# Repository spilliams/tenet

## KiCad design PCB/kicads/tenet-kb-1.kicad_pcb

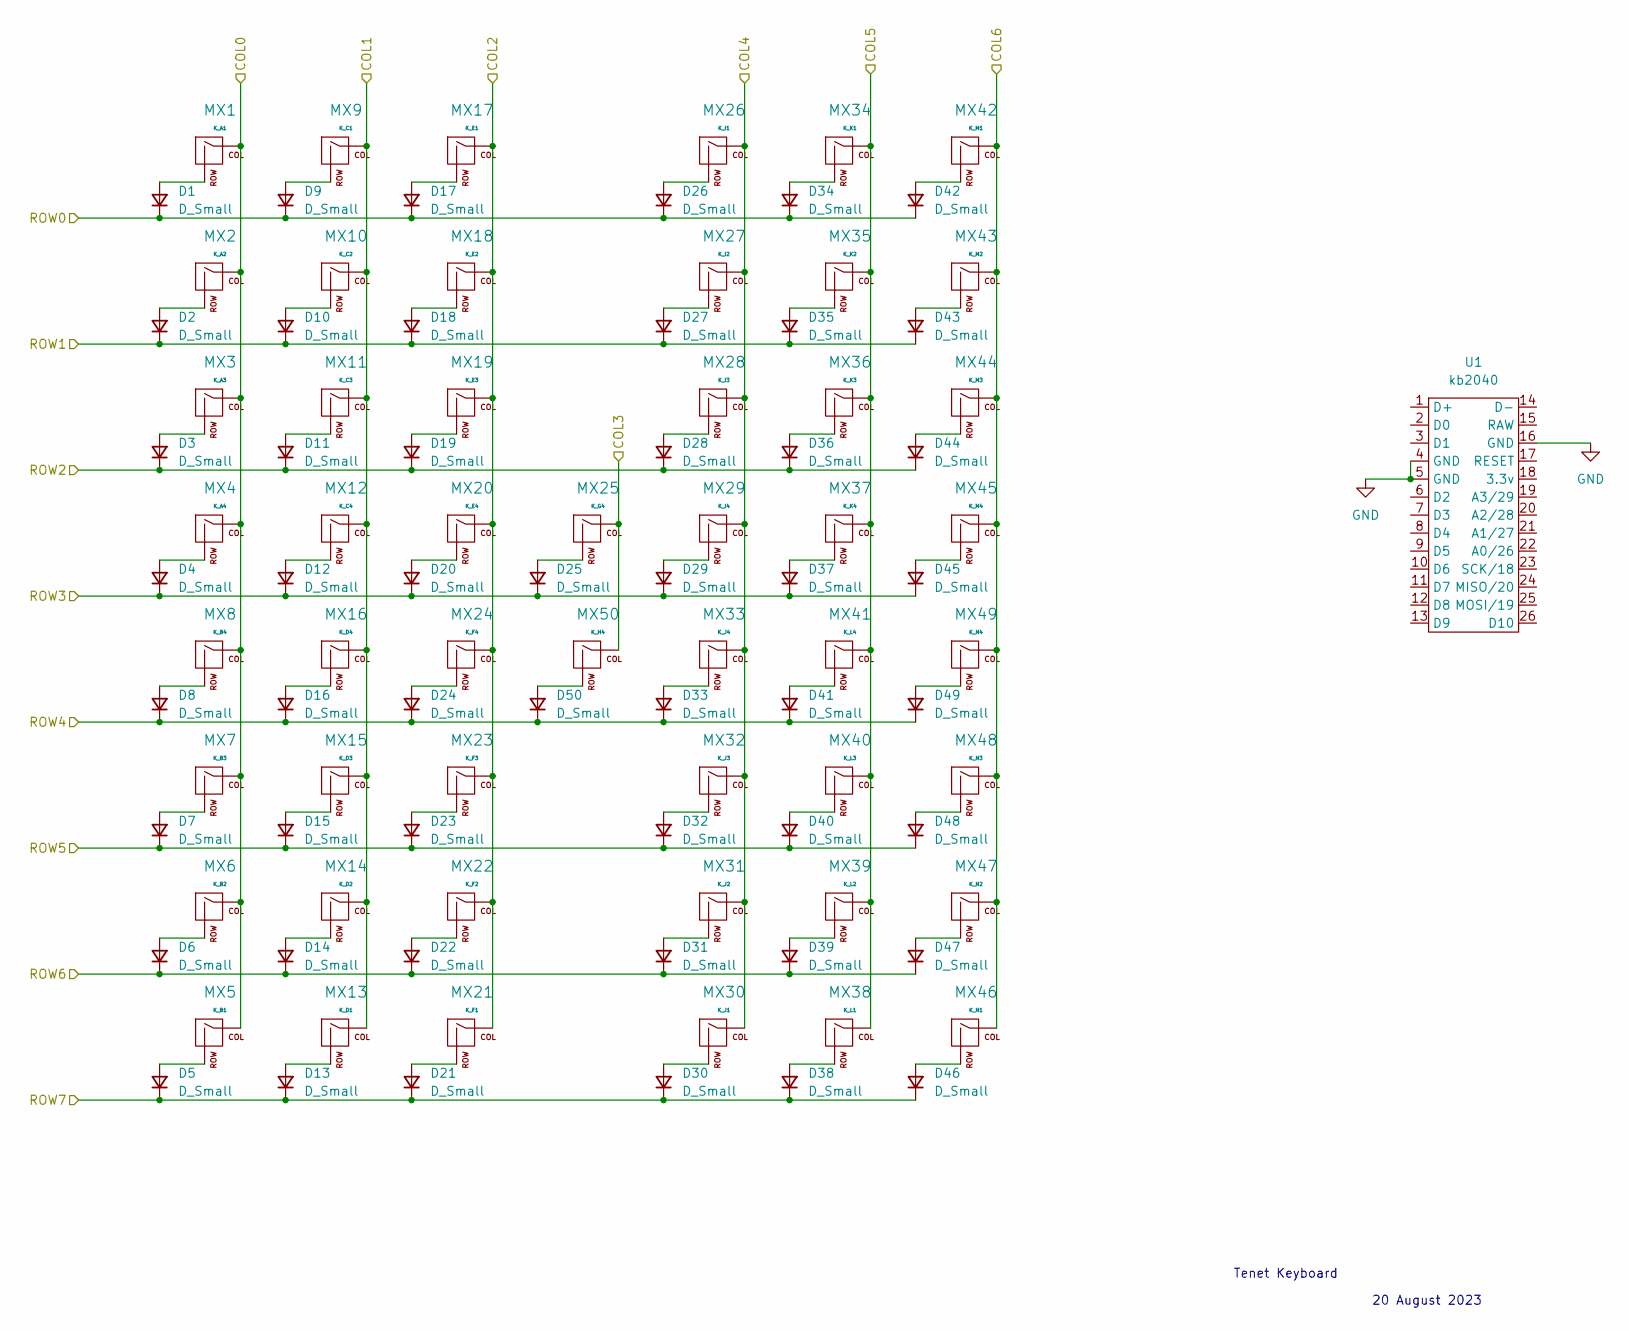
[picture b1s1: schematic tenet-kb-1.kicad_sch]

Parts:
D1, D2, D3, D4, D5, D6, D7, D8, D9, D10, D11, D12, D13, D14, D15, D16, D17, D18, D19, D20, D21, D22, D23, D24, D25, D26, D27, D28, D29, D30, D31, D32, D33, D34, D35, D36, D37, D38, D39, D40, D41, D42, D43, D44, D45, D46, D47, D48, D49, D50: D_Small; D_SOD-123
MX1: K_A1; Kailh_socket_PG1350
MX2: K_A2; Kailh_socket_PG1350
MX3: K_A3; Kailh_socket_PG1350
MX4: K_A4; Kailh_socket_PG1350
MX5: K_B1; Kailh_socket_PG1350
MX6: K_B2; Kailh_socket_PG1350
MX7: K_B3; Kailh_socket_PG1350
MX8: K_B4; Kailh_socket_PG1350
MX9: K_C1; Kailh_socket_PG1350
MX10: K_C2; Kailh_socket_PG1350
MX11: K_C3; Kailh_socket_PG1350
MX12: K_C4; Kailh_socket_PG1350
MX13: K_D1; Kailh_socket_PG1350
MX14: K_D2; Kailh_socket_PG1350
MX15: K_D3; Kailh_socket_PG1350
MX16: K_D4; Kailh_socket_PG1350
MX17: K_E1; Kailh_socket_PG1350
MX18: K_E2; Kailh_socket_PG1350
MX19: K_E3; Kailh_socket_PG1350
MX20: K_E4; Kailh_socket_PG1350
MX21: K_F1; Kailh_socket_PG1350
MX22: K_F2; Kailh_socket_PG1350
MX23: K_F3; Kailh_socket_PG1350
MX24: K_F4; Kailh_socket_PG1350
MX25: K_G4; Kailh_socket_PG1350
MX26: K_I1; Kailh_socket_PG1350
MX27: K_I2; Kailh_socket_PG1350
MX28: K_I3; Kailh_socket_PG1350
MX29: K_I4; Kailh_socket_PG1350
MX30: K_J1; Kailh_socket_PG1350
MX31: K_J2; Kailh_socket_PG1350
MX32: K_J3; Kailh_socket_PG1350
MX33: K_J4; Kailh_socket_PG1350
MX34: K_K1; Kailh_socket_PG1350
MX35: K_K2; Kailh_socket_PG1350
MX36: K_K3; Kailh_socket_PG1350
MX37: K_K4; Kailh_socket_PG1350
MX38: K_L1; Kailh_socket_PG1350
MX39: K_L2; Kailh_socket_PG1350
MX40: K_L3; Kailh_socket_PG1350
MX41: K_L4; Kailh_socket_PG1350
MX42: K_M1; Kailh_socket_PG1350
MX43: K_M2; Kailh_socket_PG1350
MX44: K_M3; Kailh_socket_PG1350
MX45: K_M4; Kailh_socket_PG1350
MX46: K_N1; Kailh_socket_PG1350
MX47: K_N2; Kailh_socket_PG1350
MX48: K_N3; Kailh_socket_PG1350
MX49: K_N4; Kailh_socket_PG1350
MX50: K_H4; Kailh_socket_PG1350
U1: kb2040

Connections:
3.3V: U1.17 (RESET)
/COL0: MX1.1 (COL), MX2.1 (COL), MX3.1 (COL), MX4.1 (COL), MX5.1 (COL), MX6.1 (COL), MX7.1 (COL), MX8.1 (COL), U1.18 (3.3v)
/COL1: MX9.1 (COL), MX10.1 (COL), MX11.1 (COL), MX12.1 (COL), MX13.1 (COL), MX14.1 (COL), MX15.1 (COL), MX16.1 (COL), U1.20 (A2/28)
/COL2: MX17.1 (COL), MX18.1 (COL), MX19.1 (COL), MX20.1 (COL), MX21.1 (COL), MX22.1 (COL), MX23.1 (COL), MX24.1 (COL), U1.11 (D7)
/COL3: MX25.1 (COL), MX50.1 (COL), U1.13 (D9)
/COL4: MX26.1 (COL), MX27.1 (COL), MX28.1 (COL), MX29.1 (COL), MX30.1 (COL), MX31.1 (COL), MX32.1 (COL), MX33.1 (COL), U1.9 (D5)
/COL5: MX34.1 (COL), MX35.1 (COL), MX36.1 (COL), MX37.1 (COL), MX38.1 (COL), MX39.1 (COL), MX40.1 (COL), MX41.1 (COL), U1.6 (D2)
/COL6: MX42.1 (COL), MX43.1 (COL), MX44.1 (COL), MX45.1 (COL), MX46.1 (COL), MX47.1 (COL), MX48.1 (COL), MX49.1 (COL), U1.2 (D0)
/ROW0: D1.1 (K), D9.1 (K), D17.1 (K), D26.1 (K), D34.1 (K), D42.1 (K), U1.16 (GND)
/ROW1: D2.1 (K), D10.1 (K), D18.1 (K), D27.1 (K), D35.1 (K), D43.1 (K), U1.8 (D4)
/ROW2: D3.1 (K), D11.1 (K), D19.1 (K), D28.1 (K), D36.1 (K), D44.1 (K), U1.12 (D8)
/ROW3: D4.1 (K), D12.1 (K), D20.1 (K), D25.1 (K), D29.1 (K), D37.1 (K), D45.1 (K), U1.7 (D3)
/ROW4: D8.1 (K), D16.1 (K), D24.1 (K), D33.1 (K), D41.1 (K), D49.1 (K), D50.1 (K), U1.13 (D9)
/ROW5: D7.1 (K), D15.1 (K), D23.1 (K), D32.1 (K), D40.1 (K), D48.1 (K), U1.10 (D6)
/ROW6: D6.1 (K), D14.1 (K), D22.1 (K), D31.1 (K), D39.1 (K), D47.1 (K), U1.3 (D1)
/ROW7: D5.1 (K), D13.1 (K), D21.1 (K), D30.1 (K), D38.1 (K), D46.1 (K), U1.19 (A3/29)
unnamed: D1.2 (A), MX1.2 (ROW)
unnamed: D2.2 (A), MX2.2 (ROW)
unnamed: D3.2 (A), MX3.2 (ROW)
unnamed: D4.2 (A), MX4.2 (ROW)
unnamed: D5.2 (A), MX5.2 (ROW)
unnamed: D6.2 (A), MX6.2 (ROW)
unnamed: D7.2 (A), MX7.2 (ROW)
unnamed: D8.2 (A), MX8.2 (ROW)
unnamed: D9.2 (A), MX9.2 (ROW)
unnamed: D10.2 (A), MX10.2 (ROW)
unnamed: D11.2 (A), MX11.2 (ROW)
unnamed: D12.2 (A), MX12.2 (ROW)
unnamed: D13.2 (A), MX13.2 (ROW)
unnamed: D14.2 (A), MX14.2 (ROW)
unnamed: D15.2 (A), MX15.2 (ROW)
unnamed: D16.2 (A), MX16.2 (ROW)
unnamed: D17.2 (A), MX17.2 (ROW)
unnamed: D18.2 (A), MX18.2 (ROW)
unnamed: D19.2 (A), MX19.2 (ROW)
unnamed: D20.2 (A), MX20.2 (ROW)
unnamed: D21.2 (A), MX21.2 (ROW)
unnamed: D22.2 (A), MX22.2 (ROW)
unnamed: D23.2 (A), MX23.2 (ROW)
unnamed: D24.2 (A), MX24.2 (ROW)
unnamed: D25.2 (A), MX25.2 (ROW)
unnamed: D26.2 (A), MX26.2 (ROW)
unnamed: D27.2 (A), MX27.2 (ROW)
unnamed: D28.2 (A), MX28.2 (ROW)
unnamed: D29.2 (A), MX29.2 (ROW)
unnamed: D30.2 (A), MX30.2 (ROW)
unnamed: D31.2 (A), MX31.2 (ROW)
unnamed: D32.2 (A), MX32.2 (ROW)
unnamed: D33.2 (A), MX33.2 (ROW)
unnamed: D34.2 (A), MX34.2 (ROW)
unnamed: D35.2 (A), MX35.2 (ROW)
unnamed: D36.2 (A), MX36.2 (ROW)
unnamed: D37.2 (A), MX37.2 (ROW)
unnamed: D38.2 (A), MX38.2 (ROW)
unnamed: D39.2 (A), MX39.2 (ROW)
unnamed: D40.2 (A), MX40.2 (ROW)
unnamed: D41.2 (A), MX41.2 (ROW)
unnamed: D42.2 (A), MX42.2 (ROW)
unnamed: D43.2 (A), MX43.2 (ROW)
unnamed: D44.2 (A), MX44.2 (ROW)
unnamed: D45.2 (A), MX45.2 (ROW)
unnamed: D46.2 (A), MX46.2 (ROW)
unnamed: D47.2 (A), MX47.2 (ROW)
unnamed: D48.2 (A), MX48.2 (ROW)
unnamed: D49.2 (A), MX49.2 (ROW)
unnamed: D50.2 (A), MX50.2 (ROW)

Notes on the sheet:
20 August 2023
Tenet Keyboard

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
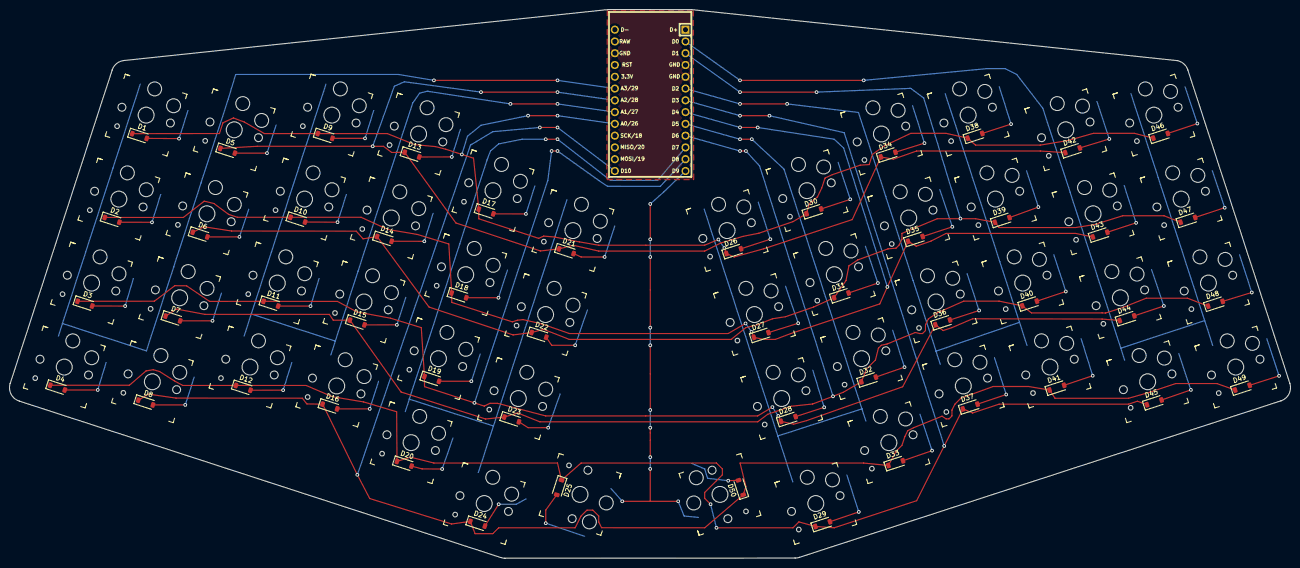
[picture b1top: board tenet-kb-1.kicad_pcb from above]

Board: 2 copper layers, 276.3 x 118.4 mm, 101 parts (1 on the bottom side), 66 nets.

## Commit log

2022-08-29 first switchplate
2022-08-30 rev2
2022-08-30 54 degrees is too much; and other tweaks
2022-11-26 display woes vanquished
2023-01-28 getting ready to publish
2023-01-28 3d files
2023-01-28 organize
2023-01-28 files for printing
2023-01-29 ready for publication
2023-01-29 updated link
2023-08-20 new empty KiCad project
2023-08-20 imported libraries
2023-08-20 MCU schematic
2023-08-20 keyswitch schematics
2023-08-20 footprints assigned
2023-08-21 pcb 1, mostly done
2024-04-21 new design start
2025-03-20 dump
